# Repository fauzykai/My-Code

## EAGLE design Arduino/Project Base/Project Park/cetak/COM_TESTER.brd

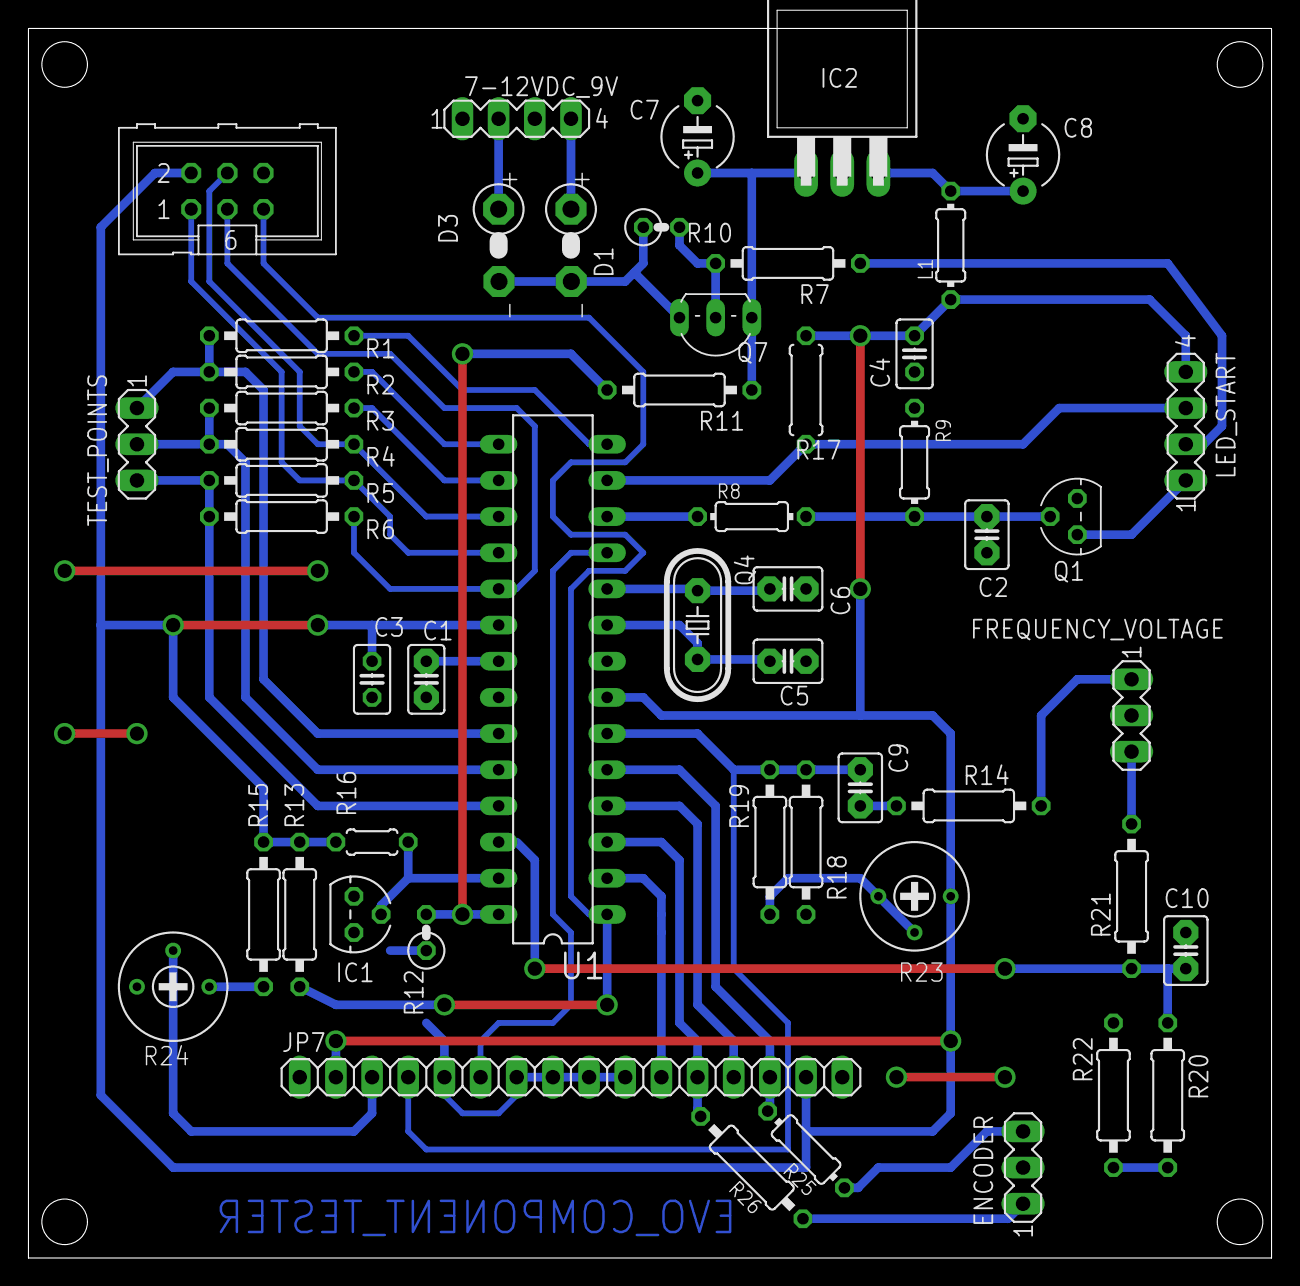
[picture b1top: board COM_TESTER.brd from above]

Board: 2 copper layers, 87.3 x 86.3 mm, 52 parts (0 on the bottom side), 44 nets.

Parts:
7-12VDC_9V: MA04-1
C1: 1nF; C2.5-2
C2: 10nF; C2.5-3
C3, C4: 100nF; C025-025X050
C5, C6: 22pF; C2.5-3
C7, C8: 2.2µF; E5-5
C9, C10: 100n; C2.5-3
D1, D3: SB130; DIODE-3-5A-V
ENCODER: MA03-1
FREQUENCY_VOLTAGE: MA03-1
IC1: LM336LP; TO92
IC2: 7805T; TO220H
JP3: ISP; ML6
JP7: LCD Display; PINHD-1X16
L1: 10µH; 0204/7
LED_START: MA04-1
Q1: BC547B; TO92
Q4: 8 MHz; HC49/S
Q7: BC328-40; TO92-EBC
R1, R3, R5: 680; 0207/10
R2, R4, R6: 470k; 0207/10
R7: 3k3; 0207/10
R8: 27k; 0204/7
R9: 100k; 0204/7
R10: 33k; 0207/2V
R11, R13, R18, R19, R20, R22: 10k; 0207/10
R12: 3k3; 0207/2V
R14: 470; 0207/10
R15: 15k; 0207/10
R16: 2k2; 0204/5
R17: 27k; 0207/7
R21: 180k; 0207/10
R23, R24: RTRIM3339P
R25: 1k; 0204/7
R26: 1k; 0207/10
TEST_POINTS: MA03-1
U1: ATmega8/168/328; DIL28-3

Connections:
+5V: C3.2, C4.1, JP3.2, JP7.2, JP7.15, L1.1, LED_START.4, R13.1, R15.1, R16.2, R17.2, R23.3, U1.7, U1.20
+9V: C7.+, IC2.1, Q7.C, R11.1
GND: 7-12VDC_9V.1, 7-12VDC_9V.3, C1.1, C2.2, C3.1, C4.2, C5.1, C6.1, C7.-, C8.-, C10.1, ENCODER.2, FREQUENCY_VOLTAGE.2, IC1.3, IC2.2, JP3.6, JP7.1, JP7.5, JP7.7, JP7.8, JP7.9, JP7.10, JP7.16, Q1.1, R9.1, R12.1, R18.1, R22.1, R24.3, U1.8, U1.22
unnamed: R15.2, R24.1
unnamed: JP7.3, R24.2
unnamed: FREQUENCY_VOLTAGE.1, R14.1
unnamed: C9.1, R14.2
unnamed: D1.C, D3.C, Q7.E, R10.1
unnamed: R19.2, R23.1, R23.2
unnamed: R20.1, R22.2
unnamed: LED_START.1, Q1.3
unnamed: 7-12VDC_9V.4, D1.A
unnamed: C1.2, U1.21
unnamed: ENCODER.3, R25.1
unnamed: C5.2, Q4.2, U1.9
unnamed: C6.2, Q4.1, U1.10
unnamed: ENCODER.1, R26.1
unnamed: FREQUENCY_VOLTAGE.3, R21.2
unnamed: C8.+, IC2.3, L1.2
unnamed: 7-12VDC_9V.2, D3.A
unnamed: Q7.B, R7.2, R10.2
unnamed: C2.1, Q1.2, R8.2, R9.2
PB0: R1.1, U1.14
PB1: R2.1, U1.15
PB2: R3.1, U1.16
PB3: JP3.4, R4.1, U1.17
PB4: JP3.1, R5.1, U1.18
PB5: JP3.3, R6.1, U1.19
PC0: R1.2, R2.2, TEST_POINTS.1, U1.23
PC1: R3.2, R4.2, TEST_POINTS.2, U1.24
PC2: R5.2, R6.2, TEST_POINTS.3, U1.25
PC3: C10.2, R20.2, R21.1, U1.26
PC4: IC1.2, R16.1, U1.27
PC5: R11.2, R12.2, U1.28
PC6: JP3.5, R13.2, U1.1
PD0: JP7.11, U1.2
PD1: JP7.12, R26.2, U1.3
PD2: JP7.13, U1.4
PD3: JP7.14, R25.2, U1.5
PD4: C9.2, JP7.4, R18.2, R19.1, U1.6
PD5: JP7.6, U1.11
PD6: R8.1, U1.12
PD7: LED_START.3, R17.1, U1.13
START: LED_START.2, R7.1

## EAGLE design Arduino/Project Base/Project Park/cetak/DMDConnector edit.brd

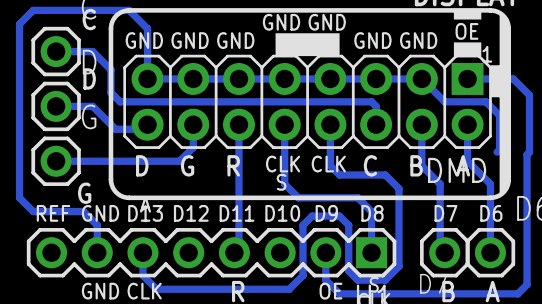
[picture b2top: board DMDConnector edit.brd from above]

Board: 2 copper layers, 8 parts (1 on the bottom side), 10 nets.

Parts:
C: M01PTH; 1X01
D, D6, D7: M01PTH; 1X01
DMD: M08X2; 2X8-SMALLERPADS
G: M01PTH; 1X01
H1: Digital_8_13; 1X08
R1: 10K; 0805

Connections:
C: C.1, DMD.6
D: D.1, DMD.16
D6: D6.1, DMD.2
D7: D7.1, DMD.4
D8: DMD.10, H1.1
D9: DMD.1, H1.2, R1.2
D11_MOSI: DMD.12, H1.4
D13_SCK: DMD.8, H1.6
G: DMD.14, G.1
GND: DMD.3, DMD.5, DMD.7, DMD.9, DMD.11, DMD.13, DMD.15, H1.7, R1.1

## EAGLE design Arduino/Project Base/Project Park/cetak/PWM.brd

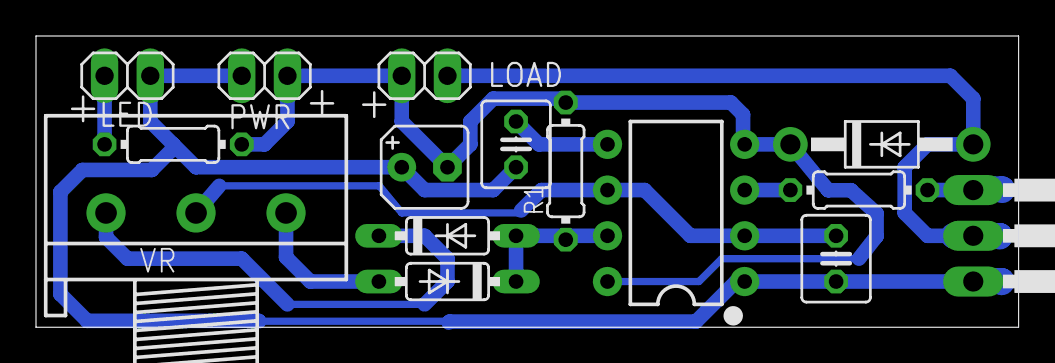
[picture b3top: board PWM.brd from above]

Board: 2 copper layers, 54.6 x 16.2 mm, 15 parts (0 on the bottom side), 11 nets.

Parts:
C1: 0.01; C025-040X050
C2: 0.1; C025-040X050
C3: B45181A
D1, D2: 4148; DO35-7
D3: 1N4004; DO41-10
IC1: 555; DIP08
LED: 1X02
LOAD: 1X02
PWR: 1X02
Q1: IRF540; TO220
R1: 0204/7
R2, R3: 330; 0204/7
VR: 50k; 3RP/1610N

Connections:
unnamed: C2.2, IC1.2, IC1.6, VR.2
unnamed: IC1.3, R2.2
unnamed: C1.2, IC1.5
unnamed: C1.1, C2.1, C3.+, IC1.1, LED.2, PWR.1, Q1.3
unnamed: D1.A, VR.3
unnamed: D2.C, VR.1
unnamed: D1.C, D2.A, IC1.7, R1.1
unnamed: LED.1, R3.1
unnamed: C3.-, D3.C, IC1.4, IC1.8, LOAD.2, PWR.2, R1.2, R3.2
unnamed: Q1.1, R2.1
unnamed: D3.A, LOAD.1, Q1.2

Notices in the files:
Arduino/Project Base/Project Park/cetak/DMDConnector edit.brd:
(C)2014 Freetronics Pty Ltd
parts and their libraries:
SparkFun-IC-Special-Function: Licensing: Creative Commons ShareAlike 4.0 International - https://creativecommons.org/licenses/by-sa/4.0
